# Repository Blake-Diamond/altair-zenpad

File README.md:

# UC Santa Barbara - ECE Department 
## EE Capstone 2018-2019

### Contributors: Evan Blasband, Blake Diamond, Adam Gulliver, Zack Klebanoff

https://capstone.engineering.ucsb.edu/projects/altair-zenpad

This repository contains all of our arduino and android studio code for Altair Zenpad, a smart massage pad that you can control from your fingertips. There are 3 imporant aspect of this respository that contiain all of the necessary reference documents for future development and use of the ZenPad, described below:

## Hardware

PCB/Altair Massage Pad: contains all PCB projects (EAGLE) for Main and Peripheral PCB.

## Firmware

Winter_Demo: This folder contains all of the firmware that is need to flash the Teensy 3.6 using the Arduino IDE. This includes all associated header files that support use of the Bluetooth and PMIC. Some small changes are needed in order to program a Teensy board with the Arduino IDE, which can be found here: https://www.pjrc.com/teensy/tutorial.html

## Software

Zenpad-App/ZenPad: This folder contains the software project for the ZenPad app, which can be accessed by downloading and opening with Android Studio. Someone with Android SW development experience is needed in order to properly open and run the app, which was developed on a Nexus 5 phone.

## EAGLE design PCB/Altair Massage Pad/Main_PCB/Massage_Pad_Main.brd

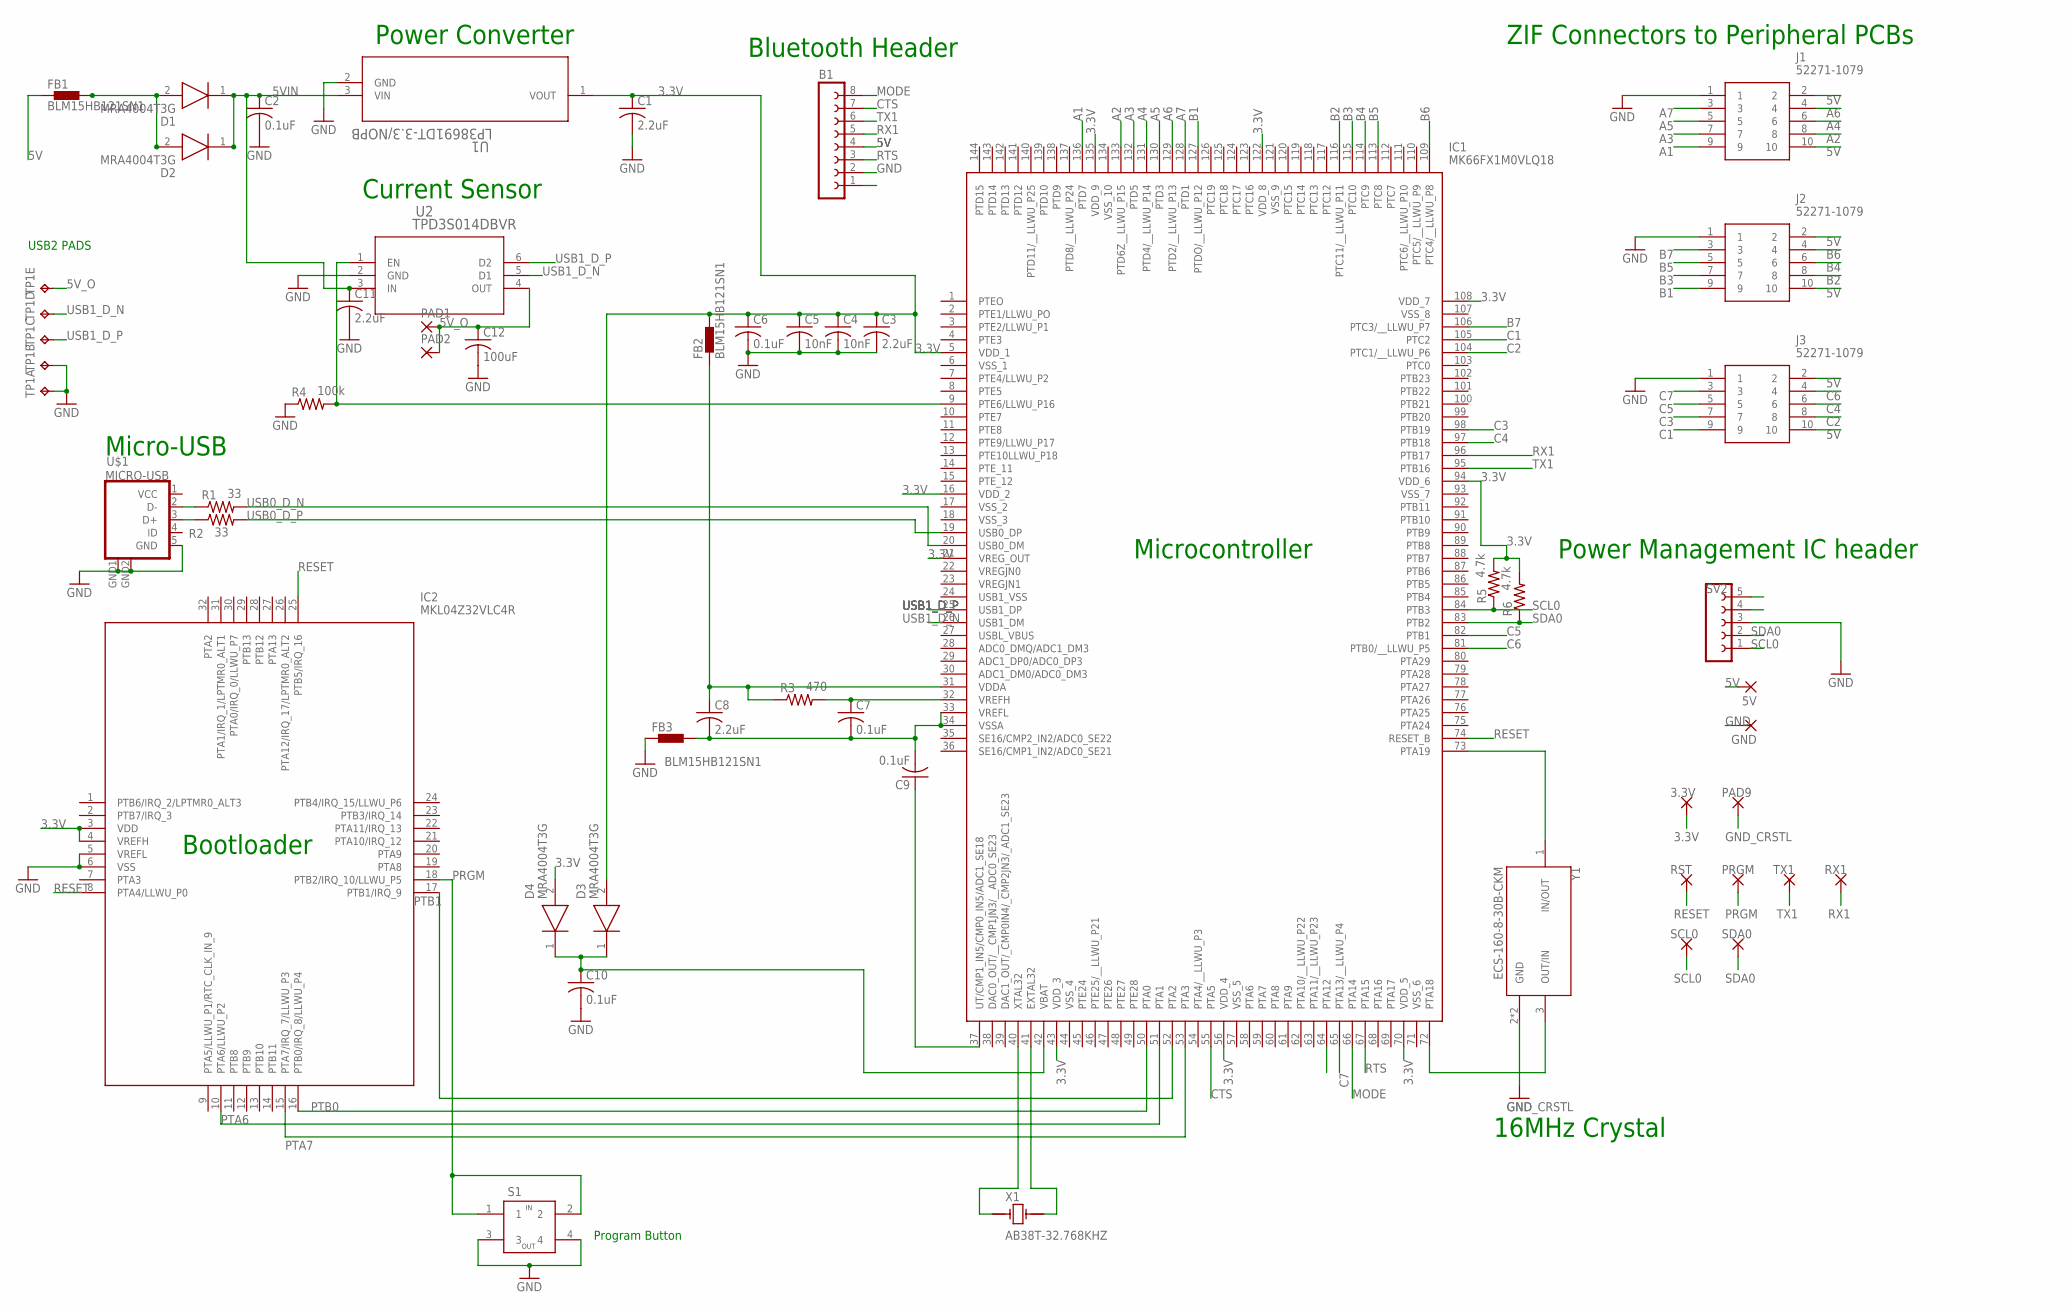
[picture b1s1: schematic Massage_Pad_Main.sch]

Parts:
3.3V: 1,6/0,8
5V: 3,17/1,3
B1: BT-BLE-2479
C1, C3, C8, C11: 2.2uF; C1812K
C2, C6, C7, C9, C10: 0.1uF; C1808
C4, C5: 10nF; C1808
C12: 100uF; C1210K
D1, D2, D3, D4: MRA4004T3G; DIOM5226X220N
FB1, FB2, FB3: BLM15HB121SN1; 0402
GND: 3,17/1,3
IC1: MK66FX1M0VLQ18; QFP50P2200X2200X160-144N
IC2: MKL04Z32VLC4R; QFP80P900X900X160-32N
J1, J2, J3: 52271-1079
PAD1, PAD2: SMD5; SMD2,54-5,08
PAD9: 1,6/0,8
PRGM: 1,6/0,8
R1, R2: 33; R1206
R3: 470; R1206
R4: 100k; R1206
R5, R6: 4.7k; R1206
RST: 1,6/0,8
RX1: 1,6/0,8
S1: RS-187R05A2-DSMTRT
SCL0: 1,6/0,8
SDA0: 1,6/0,8
SV2: FE05-1
TP1: TP5P5-25-13; P5-25-13
TX1: 1,6/0,8
U1: LP38691DT-3.3/NOPB; TD03B
U2: TPD3S014DBVR; DBV6
U$1: MICRO-USB
X1: AB38T-32.768KHZ; XTAL_AB38T-32.768KHZ
Y1: ECS-160-8-30B-CKM; XTAL_ECS-160-8-30B-CKM

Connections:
3.3V: 3.3V.1, C1.1, C3.1, C4.1, C5.1, C6.1, D3.2 (A), D4.2 (A), FB2.2, IC1.5 (VDD_1), IC1.16 (VDD_2), IC1.21 (VREG_OUT), IC1.43 (VDD_3), IC1.56 (VDD_4), IC1.70 (VDD_5), IC1.94 (VDD_6), IC1.108 (VDD_7), IC1.122 (VDD_8), IC1.135 (VDD_9), IC2.3 (VDD), IC2.4 (VREFH), R5.2, R6.2, U1.1 (VOUT)
5V: 5V.1, B1.4, FB1.1, J1.2, J1.10, J2.2, J2.10, J3.2, J3.10
5VIN: C2.1, C11.1, D1.1 (K), D2.1 (K), U1.3 (VIN), U2.3 (IN)
5V_O: C12.1, PAD1.1, PAD2.1, TP1.TP-5, U2.4 (OUT)
A1: IC1.136 (PTD7), J1.9
A2: IC1.133 (PTD6Z__LLWU_P15), J1.8
A3: IC1.132 (PTD5), J1.7
A4: IC1.131 (PTD4/__LLWU_P14), J1.6
A5: IC1.130 (PTD3), J1.5
A6: IC1.129 (PTD2/__LLWU_P13), J1.4
A7: IC1.128 (PTD1), J1.3
B1: IC1.127 (PTDO/__LLWU_P12), J2.9
B2: IC1.116 (PTC11/__LLWU_P11), J2.8
B3: IC1.115 (PTC10), J2.7
B4: IC1.114 (PTC9), J2.6
B5: IC1.113 (PTC8), J2.5
B6: IC1.109 (PTC4/__LLWU_P8), J2.4
B7: IC1.106 (PTC3/__LLWU_P7), J2.3
C1: IC1.105 (PTC2), J3.9
C2: IC1.104 (PTC1/__LLWU_P6), J3.8
C3: IC1.98 (PTB19), J3.7
C4: IC1.97 (PTB18), J3.6
C5: IC1.82 (PTB1), J3.5
C6: IC1.81 (PTB0/__LLWU_P5), J3.4
C7: IC1.65 (PTA13/__LLWU_P4), J3.3
CTS: B1.7, IC1.55 (PTA5)
DFU_5V: B1.1
GND: B1.2, C1.2, C2.2, C3.2, C4.2, C5.2, C6.2, C10.2, C11.2, C12.2, FB3.1, GND.1, IC2.5 (VREFL), IC2.6 (VSS), J1.1, J2.1, J3.1, R4.1, S1.3, S1.4, SV2.3, TP1.TP-1, TP1.TP-2, U1.2 (GND), U2.2 (GND), U$1.5 (GND), U$1.GND1 (GND), U$1.GND2 (GND)
GND_CRSTL: PAD9.1, Y1.2 (GND), Y1.4 (GND)
MODE: B1.8, IC1.66 (PTA14)
unnamed: C10.1, D3.1 (K), D4.1 (K), IC1.42 (VBAT)
unnamed: R1.1, U$1.2 (D-)
unnamed: R2.1, U$1.3 (D+)
unnamed: D1.2 (A), D2.2 (A), FB1.2
unnamed: IC1.73 (PTA19), Y1.1 (IN/OUT)
unnamed: C7.1, IC1.32 (VREFH), R3.2
unnamed: C7.2, C8.2, C9.2, FB3.2, IC1.33 (VREFL), IC1.34 (VSSA)
unnamed: C8.1, FB2.1, IC1.31 (VDDA), R3.1
unnamed: C9.1, IC1.37 (UT/CMP1_IN5/CMP0_IN5/ADC1_SE18)
unnamed: IC1.72 (PTA18), Y1.3 (OUT/IN)
unnamed: IC1.40 (XTAL32), X1.1
unnamed: IC1.41 (EXTAL32), X1.2
unnamed: IC1.9 (PTE6/LLWU_P16), R4.2, U2.1 (EN)
PRGM: IC2.18 (PTB2/IRQ_10/LLWU_P5), PRGM.1, S1.1, S1.2
PTA6: IC1.51 (PTA1), IC2.10 (PTA6/LLWU_P2)
PTA7: IC1.53 (PTA3), IC2.15 (PTA7/IRQ_7/LLWU_P3)
PTB0: IC1.50 (PTA0), IC2.16 (PTB0/IRQ_8/LLWU_P4)
PTB1: IC1.52 (PTA2), IC2.17 (PTB1/IRQ_9)
RESET: IC1.74 (RESET_B), IC2.8 (PTA4/LLWU_P0), IC2.25 (PTB5/IRQ_16), RST.1
RTS: B1.3, IC1.67 (PTA15)
RX1: B1.5, IC1.96 (PTB17), RX1.1
SCL0: IC1.84 (PTB3), R5.1, SCL0.1, SV2.1
SDA0: IC1.83 (PTB2), R6.1, SDA0.1, SV2.2
TX1: B1.6, IC1.95 (PTB16), TX1.1
USB0_D_N: IC1.20 (USB0_DM), R1.2
USB0_D_P: IC1.19 (USB0_DP), R2.2
USB1_D_N: IC1.26 (USB1_DM), TP1.TP-4, U2.5 (D1)
USB1_D_P: IC1.25 (USB1_DP), TP1.TP-3, U2.6 (D2)
VCC: U$1.1 (VCC)

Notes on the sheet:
Bluetooth Header
ZIF Connectors to Peripheral PCBs
Microcontroller
Bootloader
Micro-USB
Power Converter
Current Sensor
Power Management IC header
16MHz Crystal
Program Button
USB2 PADS

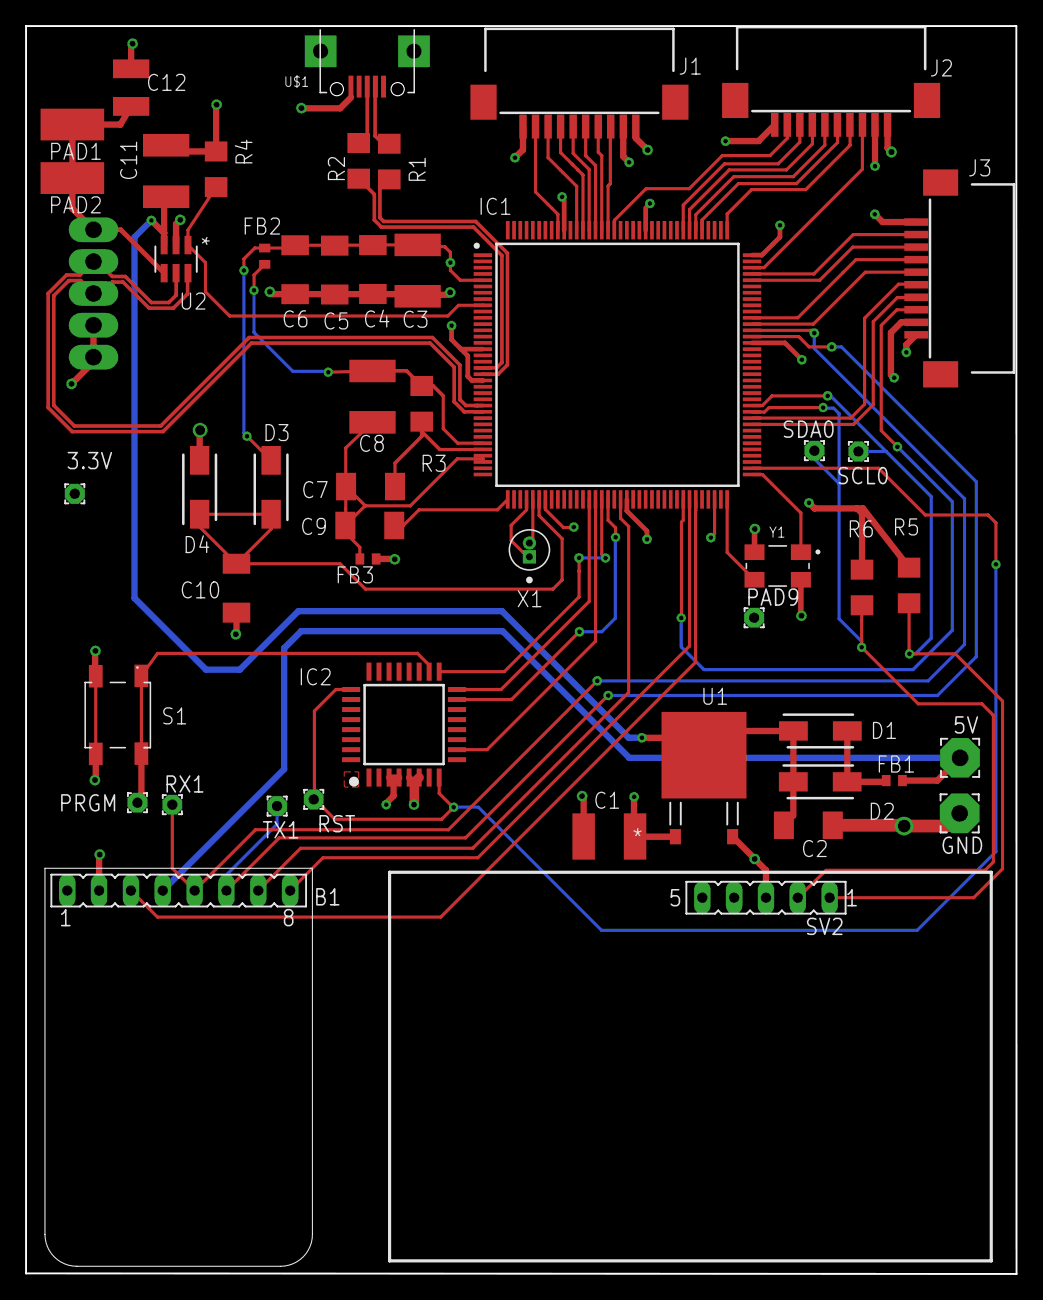
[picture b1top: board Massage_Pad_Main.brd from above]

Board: 4 copper layers, 79.0 x 99.6 mm, 51 parts (0 on the bottom side), 57 nets.

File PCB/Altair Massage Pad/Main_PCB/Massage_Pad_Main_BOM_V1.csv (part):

"Part";"Value";"Device";"Package";"Description";"ALLIED_NUMBER";"ALLIED_PRICE-STOCK";"DESCRIPTION";"DIGI-KEY_PART_NUMBER";"DIGI-KEY_PURCHASE_URL";"HEIGHT";"MANUFACTURER_NAME";"MANUFACTURER_PART_NUMBER";"MF";"MOUSER_PART_NUMBER";"MOUSER_PRICE-STOCK";"MP";"MPN";"OC_FARNELL";"OC_NEWARK";"PACKAGE";"RS_PART_NUMBER";"RS_PRICE-STOCK";"SPICEPREFIX";"TP_SIGNAL_NAME";"VENDOR";
"3.3V";"";"1,6/0,8";"1,6/0,8";"THROUGH-HOLE PAD";"";"";"";"";"";"";"";"";"";"";"";"";"";"";"";"";"";"";"";"";"";
"5V";"";"3,17/1,3";"3,17/1,3";"THROUGH-HOLE PAD";"";"";"";"";"";"";"";"";"";"";"";"";"";"";"";"";"";"";"";"";"";
"B1";"";"BT-BLE-2479";"BT-BLE-2479";"Adafruit bluetooth BLE module for mounting onto PCB.";"";"";"";"";"";"";"";"";"";"";"";"";"";"";"";"";"";"";"";"";"";
"C1";"2.2uF";"C-USC1808";"C1808";"CAPACITOR, American symbol";"";"";"";"";"";"";"";"";"";"";"";"";"";"";"";"";"";"";"C";"";"";
"C2";"0.1uF";"C-USC1808";"C1808";"CAPACITOR, American symbol";"";"";"";"";"";"";"";"";"";"";"";"";"";"";"";"";"";"";"C";"";"";
"C3";"2.2uF";"C-USC1808";"C1808";"CAPACITOR, American symbol";"";"";"";"";"";"";"";"";"";"";"";"";"";"";"";"";"";"";"C";"";"";
"C4";"10nF";"C-USC1808";"C1808";"CAPACITOR, American symbol";"";"";"";"";"";"";"";"";"";"";"";"";"";"";"";"";"";"";"C";"";"";
"C5";"10nF";"C-USC1808";"C1808";"CAPACITOR, American symbol";"";"";"";"";"";"";"";"";"";"";"";"";"";"";"";"";"";"";"C";"";"";
"C6";"0.1uF";"C-USC1808";"C1808";"CAPACITOR, American symbol";"";"";"";"";"";"";"";"";"";"";"";"";"";"";"";"";"";"";"C";"";"";
"C7";"0.1uF";"C-USC1808";"C1808";"CAPACITOR, American symbol";"";"";"";"";"";"";"";"";"";"";"";"";"";"";"";"";"";"";"C";"";"";
"C8";"2.2uF";"C-USC1808";"C1808";"CAPACITOR, American symbol";"";"";"";"";"";"";"";"";"";"";"";"";"";"";"";"";"";"";"C";"";"";
"C9";"0.1uF";"C-USC1808";"C1808";"CAPACITOR, American symbol";"";"";"";"";"";"";"";"";"";"";"";"";"";"";"";"";"";"";"C";"";"";
"C10";"0.1uF";"C-USC1808";"C1808";"CAPACITOR, American symbol";"";"";"";"";"";"";"";"";"";"";"";"";"";"";"";"";"";"";"C";"";"";
"C11";"2.2uF";"C-USC1808";"C1808";"CAPACITOR, American symbol";"";"";"";"";"";"";"";"";"";"";"";"";"";"";"";"";"";"";"C";"";"";
"C12";"100uF";"C-USC1808";"C1808";"CAPACITOR, American symbol";"";"";"";"";"";"";"";"";"";"";"";"";"";"";"";"";"";"";"C";"";"";
"D1";"MRA4004T3G";"MRA4004T3G";"DIOM5226X220N";"Rectifier diode,MRA4004 1A 400V ON Semi MRA4004T3G, SMT Switching Diode, 400V 1A, 2-Pin DO-214AC";"70340468";"http://www.alliedelec.com/on-semiconductor-mra4004t3g/70340468/";"Rectifier diode,MRA4004 1A 400V ON Semi MRA4004T3G, SMT Switching Diode, 400V 1A, 2-Pin DO-214AC";"";"";"2.2mm";"ON Semiconductor";"MRA4004T3G";"";"863-MRA4004T3G";"https://www.mouser.com/Search/Refine.aspx?Keyword=863-MRA4004T3G";"";"";"";"";"";"6490904";"http://uk.rs-online.com/web/p/products/6490904";"";"";"";
"D2";"MRA4004T3G";"MRA4004T3G";"DIOM5226X220N";"Rectifier diode,MRA4004 1A 400V ON Semi MRA4004T3G, SMT Switching Diode, 400V 1A, 2-Pin DO-214AC";"70340468";"http://www.alliedelec.com/on-semiconductor-mra4004t3g/70340468/";"Rectifier diode,MRA4004 1A 400V ON Semi MRA4004T3G, SMT Switching Diode, 400V 1A, 2-Pin DO-214AC";"";"";"2.2mm";"ON Semiconductor";"MRA4004T3G";"";"863-MRA4004T3G";"https://www.mouser.com/Search/Refine.aspx?Keyword=863-MRA4004T3G";"";"";"";"";"";"6490904";"http://uk.rs-online.com/web/p/products/6490904";"";"";"";
"D3";"MRA4004T3G";"MRA4004T3G";"DIOM5226X220N";"Rectifier diode,MRA4004 1A 400V ON Semi MRA4004T3G, SMT Switching Diode, 400V 1A, 2-Pin DO-214AC";"70340468";"http://www.alliedelec.com/on-semiconductor-mra4004t3g/70340468/";"Rectifier diode,MRA4004 1A 400V ON Semi MRA4004T3G, SMT Switching Diode, 400V 1A, 2-Pin DO-214AC";"";"";"2.2mm";"ON Semiconductor";"MRA4004T3G";"";"863-MRA4004T3G";"https://www.mouser.com/Search/Refine.aspx?Keyword=863-MRA4004T3G";"";"";"";"";"";"6490904";"http://uk.rs-online.com/web/p/products/6490904";"";"";"";
"D4";"MRA4004T3G";"MRA4004T3G";"DIOM5226X220N";"Rectifier diode,MRA4004 1A 400V ON Semi MRA4004T3G, SMT Switching Diode, 400V 1A, 2-Pin DO-214AC";"70340468";"http://www.alliedelec.com/on-semiconductor-mra4004t3g/70340468/";"Rectifier diode,MRA4004 1A 400V ON Semi MRA4004T3G, SMT Switching Diode, 400V 1A, 2-Pin DO-214AC";"";"";"2.2mm";"ON Semiconductor";"MRA4004T3G";"";"863-MRA4004T3G";"https://www.mouser.com/Search/Refine.aspx?Keyword=863-MRA4004T3G";"";"";"";"";"";"6490904";"http://uk.rs-online.com/web/p/products/6490904";"";"";"";
"FB1";"BLM15HB121SN1";"BLM15HB121SN1";"0402";"EMIFIL (R) Chip Ferrite Bead for GHz Noise";"";"";"";"";"";"";"";"";"";"";"";"";"";"";"";"";"";"";"";"";"";
"FB2";"BLM15HB121SN1";"BLM15HB121SN1";"0402";"EMIFIL (R) Chip Ferrite Bead for GHz Noise";"";"";"";"";"";"";"";"";"";"";"";"";"";"";"";"";"";"";"";"";"";
"FB3";"BLM15HB121SN1";"BLM15HB121SN1";"0402";"EMIFIL (R) Chip Ferrite Bead for GHz Noise";"";"";"";"";"";"";"";"";"";"";"";"";"";"";"";"";"";"";"";"";"";
"GND";"";"3,17/1,3";"3,17/1,3";"THROUGH-HOLE PAD";"";"";"";"";"";"";"";"";"";"";"";"";"";"";"";"";"";"";"";"";"";
"IC1";"MK66FX1M0VLQ18";"MK66FX1M0VLQ18";"QFP50P2200X2200X160-144N";"NXP - MK66FX1M0VLQ18 - MPU, ARM CORTEX-M4F, 180MHZ, LQFP-144";"";"";"NXP - MK66FX1M0VLQ18 - MPU, ARM CORTEX-M4F, 180MHZ, LQFP-144";"";"";"1.6mm";"Nexperia";"MK66FX1M0VLQ18";"";"841-MK66FX1M0VLQ18";"https://www.mouser.com/Search/Refine.aspx?Keyword=841-MK66FX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";"";"";"";"";"";"";"";"";"";"";
"IC2";"MKL04Z32VLC4R";"MKL04Z32VLC4R";"QFP80P900X900X160-32N";"IC MCU 32BIT 32KB FLASH 32LQFP";"";"";"IC MCU 32BIT 32KB FLASH 32LQFP";"";"";"1.6mm";"Nexperia";"MKL04Z32VLC4R";"";"N/A";"https://www.mouser.com/Search/Refine.aspx?Keyword=N%2FA";"";"";"";"";"";"";"";"";"";"";
"J1";"52271-1079";"52271-1079";"52271-1079";"1.0MM FPC  R/A CONN 10 W Molex FFC/FPC SMT Series 1mm Pitch 10 Way Right Angle SMT Female FPC Connector, ZIF Bottom Contact";"70373119";"https://www.alliedelec.com/molex-incorporated-52271-1079/70373119/";"1.0MM FPC  R/A CONN 10 W Molex FFC/FPC SMT Series 1mm Pitch 10 Way Right Angle SMT Female FPC Connector, ZIF Bottom Contact";"";"";"mm";"Molex";"52271-1079";"";"538-52271-1079";"https://www.mouser.com/Search/Refine.aspx?Keyword=538-52271-1079";"";"";"";"";"";"5144329P";"http://uk.rs-online.com/web/p/products/5144329P";"";"";"";
"J2";"52271-1079";"52271-1079";"52271-1079";"1.0MM FPC  R/A CONN 10 W Molex FFC/FPC SMT Series 1mm Pitch 10 Way Right Angle SMT Female FPC Connector, ZIF Bottom Contact";"70373119";"https://www.alliedelec.com/molex-incorporated-52271-1079/70373119/";"1.0MM FPC  R/A CONN 10 W Molex FFC/FPC SMT Series 1mm Pitch 10 Way Right Angle SMT Female FPC Connector, ZIF Bottom Contact";"";"";"mm";"Molex";"52271-1079";"";"538-52271-1079";"https://www.mouser.com/Search/Refine.aspx?Keyword=538-52271-1079";"";"";"";"";"";"5144329P";"http://uk.rs-online.com/web/p/products/5144329P";"";"";"";
"J3";"52271-1079";"52271-1079";"52271-1079";"1.0MM FPC  R/A CONN 10 W Molex FFC/FPC SMT Series 1mm Pitch 10 Way Right Angle SMT Female FPC Connector, ZIF Bottom Contact";"70373119";"https://www.alliedelec.com/molex-incorporated-52271-1079/70373119/";"1.0MM FPC  R/A CONN 10 W Molex FFC/FPC SMT Series 1mm Pitch 10 Way Right Angle SMT Female FPC Connector, ZIF Bottom Contact";"";"";"mm";"Molex";"52271-1079";"";"538-52271-1079";"https://www.mouser.com/Search/Refine.aspx?Keyword=538-52271-1079";"";"";"";"";"";"5144329P";"http://uk.rs-online.com/web/p/products/5144329P";"";"";"";
"PAD1";"";"SMD5";"SMD2,54-5,08";"SMD PAD";"";"";"";"";"";"";"";"";"";"";"";"";"";"";"";"";"";"";"";"";"";
"PAD2";"";"SMD5";"SMD2,54-5,08";"SMD PAD";"";"";"";"";"";"";"";"";"";"";"";"";"";"";"";"";"";"";"";"";"";
"PAD9";"";"1,6/0,8";"1,6/0,8";"THROUGH-HOLE PAD";"";"";"";"";"";"";"";"";"";"";"";"";"";"";"";"";"";"";"";"";"";
"PRGM";"";"1,6/0,8";"1,6/0,8";"THROUGH-HOLE PAD";"";"";"";"";"";"";"";"";"";"";"";"";"";"";"";"";"";"";"";"";"";
"R1";"33";"R-EU_MELF0207W";"MINI_MELF-0207W";"RESISTOR, European symbol";"";"";"";"";"";"";"";"";"";"";"";"";"";"";"";"";"";"";"";"";"";
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
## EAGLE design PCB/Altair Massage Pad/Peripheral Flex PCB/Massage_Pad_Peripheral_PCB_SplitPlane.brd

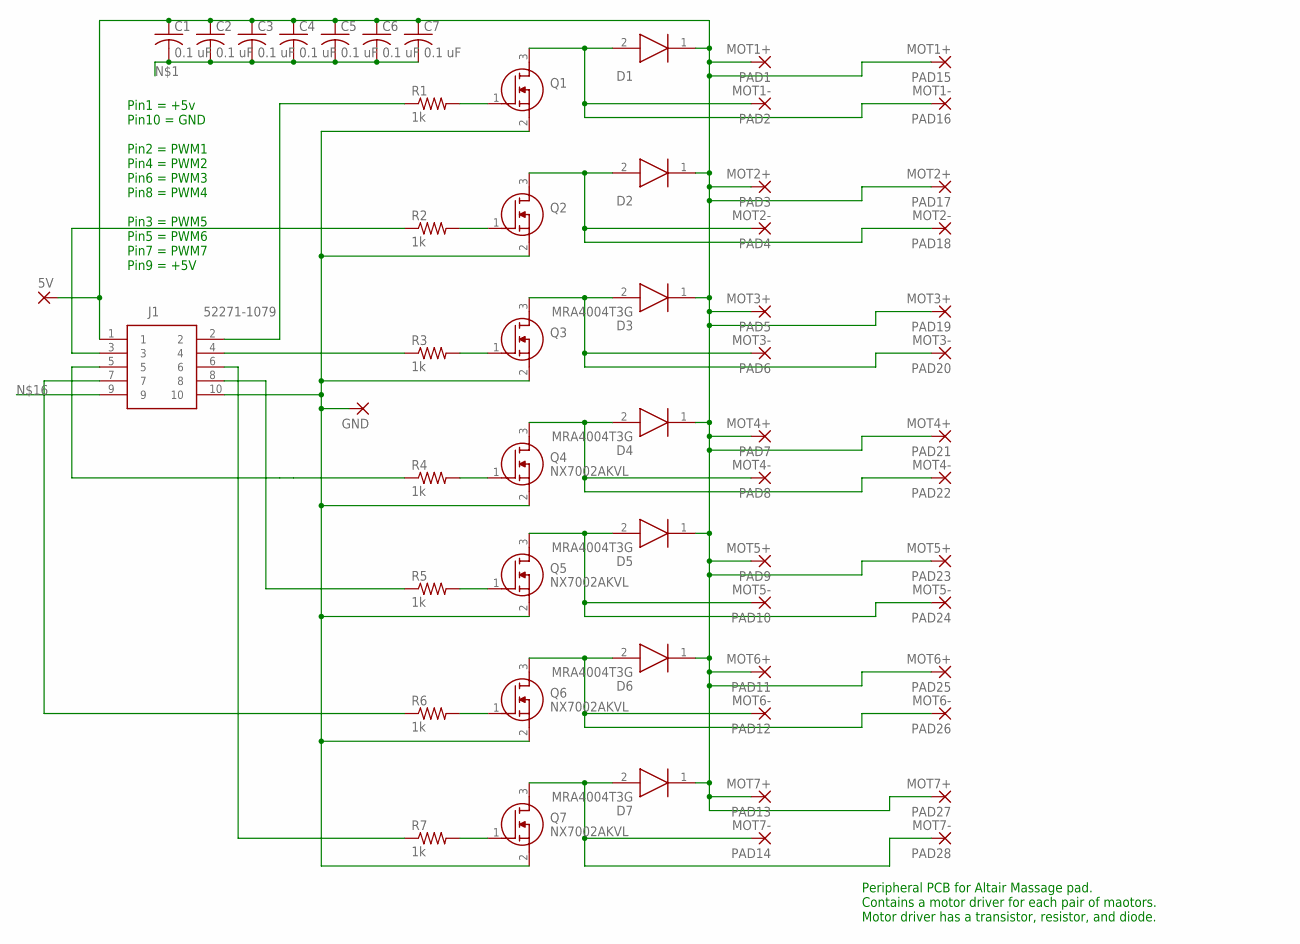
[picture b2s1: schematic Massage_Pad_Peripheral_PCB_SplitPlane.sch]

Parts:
5V: 3,17/1,3
C1, C2, C3, C4, C5, C6, C7: 0.1 uF; C1808; MANUFACTURER_PART_NUMBER C1808C104K5RACTU; MOUSER_PART_NUMBER 80-C1808C104K5R
D1, D2, D3, D4, D5, D6, D7: MRA4004T3G; DIOM5226X220N
GND: 3,17/1,3
J1: 52271-1079
PAD1, PAD15: MOT1+; 5-2,5
PAD2, PAD16: MOT1-; 5-2,5
PAD3, PAD17: MOT2+; 5-2,5
PAD4, PAD18: MOT2-; 5-2,5
PAD5, PAD19: MOT3+; 5-2,5
PAD6, PAD20: MOT3-; 5-2,5
PAD7, PAD21: MOT4+; 5-2,5
PAD8, PAD22: MOT4-; 5-2,5
PAD9, PAD23: MOT5+; 5-2,5
PAD10, PAD24: MOT5-; 5-2,5
PAD11, PAD25: MOT6+; 5-2,5
PAD12, PAD26: MOT6-; 5-2,5
PAD13, PAD27: MOT7+; 5-2,5
PAD14, PAD28: MOT7-; 5-2,5
Q1, Q2, Q3, Q4, Q5, Q6, Q7: NX7002AKVL; SOT95P230X110-3N
R1: 1k; R1206; MANUFACTURER_PART_NUMBER CR1206-FX-1001ELF; MOUSER_PART_NUMBER 652-CR1206FX-1001ELF
R2, R3, R4, R5, R6, R7: 1k; R1206

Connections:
unnamed: C1.2, C2.2, C3.2, C4.2, C5.2, C6.2, C7.2, GND.1, J1.10, Q1.2 (S), Q2.2 (S), Q3.2 (S), Q4.2 (S), Q5.2 (S), Q6.2 (S), Q7.2 (S)
unnamed: Q1.1 (G), R1.2
unnamed: Q2.1 (G), R2.2
unnamed: Q3.1 (G), R3.2
unnamed: Q4.1 (G), R4.2
unnamed: Q5.1 (G), R5.2
unnamed: Q6.1 (G), R6.2
unnamed: Q7.1 (G), R7.2
unnamed: D7.2 (A), PAD14.1, PAD28.1, Q7.3 (D)
unnamed: D6.2 (A), PAD12.1, PAD26.1, Q6.3 (D)
unnamed: D5.2 (A), PAD10.1, PAD24.1, Q5.3 (D)
unnamed: D3.2 (A), PAD6.1, PAD20.1, Q3.3 (D)
unnamed: D4.2 (A), PAD8.1, PAD22.1, Q4.3 (D)
unnamed: D2.2 (A), PAD4.1, PAD18.1, Q2.3 (D)
unnamed: D1.2 (A), PAD2.1, PAD16.1, Q1.3 (D)
unnamed: 5V.1, C1.1, C2.1, C3.1, C4.1, C5.1, C6.1, C7.1, D1.1 (K), D2.1 (K), D3.1 (K), D4.1 (K), D5.1 (K), D6.1 (K), D7.1 (K), J1.1, J1.9, PAD1.1, PAD3.1, PAD5.1, PAD7.1, PAD9.1, PAD11.1, PAD13.1, PAD15.1, PAD17.1, PAD19.1, PAD21.1, PAD23.1, PAD25.1, PAD27.1
unnamed: J1.2, R1.1
unnamed: J1.3, R2.1
unnamed: J1.4, R3.1
unnamed: J1.5, R4.1
unnamed: J1.8, R5.1
unnamed: J1.7, R6.1
unnamed: J1.6, R7.1

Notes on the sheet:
Peripheral PCB for Altair Massage pad. Contains a motor driver for each pair of maotors. Motor driver has a transistor, resistor, and diode.
Pin1 = +5v Pin10 = GND Pin2 = PWM1 Pin4 = PWM2 Pin6 = PWM3 Pin8 = PWM4 Pin3 = PWM5 Pin5 = PWM6 Pin7 = PWM7 Pin9 = +5V

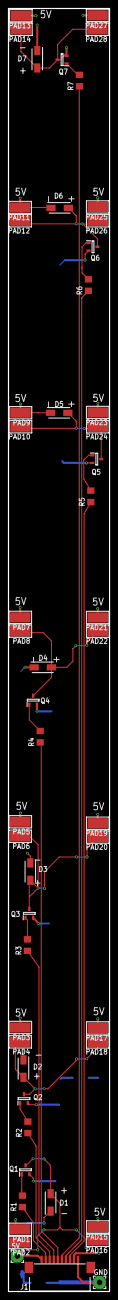
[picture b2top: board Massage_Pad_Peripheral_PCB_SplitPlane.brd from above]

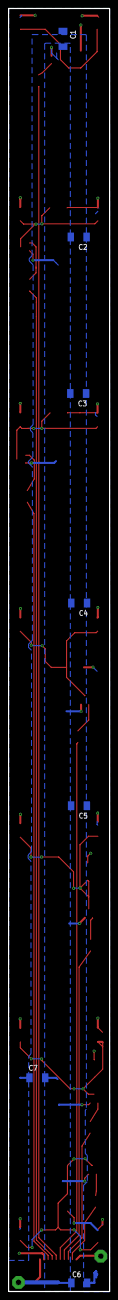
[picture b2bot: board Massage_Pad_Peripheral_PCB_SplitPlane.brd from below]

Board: 2 copper layers, 25.0 x 317.5 mm, 59 parts (7 on the bottom side), 23 nets.

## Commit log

2019-03-17 bluefruit example
2019-03-17 Rename BluefruitConfig.h to Bluetooth/BluefruitConfig.h
2019-03-17 reorganize
2019-03-17 Rename PMIC.h to PMIC/PMIC.h
2019-03-19 moved file into folder
2019-03-21 explanation
2019-03-21 3/20/19
2019-05-13 Create Zenpad-Android-App
2019-05-13 Create ZenPad-Bluetooth-Demo
2019-05-13 Create test
2019-05-14 Add files via upload
    Updates to Teensy firmware to read and print multiple bytes sent from BLE. Added needed adafruit library for arduino compatibility
2019-05-14 slight android updates to send multiple bytes via BLE
2019-05-14 Files for main PCB and Peripheral PCB sent for fab
2019-05-15 Template App for ZenPad
2019-05-17 integrated layout with BLE capability, still incomplete
2019-05-19 prints basic characters from app
2019-05-20 seekbar scaling and firmware cases handled
2019-05-21 custom activity ready for test, FW has all branches
2019-05-21 functionally complete, not tested
2019-05-22 functionally complete & tested, UI needs improvement
2019-05-22 firmware complete with patterns, needs testing
2019-05-22 removed while loop bug
2019-05-23 added onClick for all buttons, fixed FAB color
2019-05-29 code from altair demo
2019-05-30 check Vertical Wave, could try interrupt on RTS
2019-06-05 Improved Vertical Wave
2019-06-06 Small update to the pattern calls to chek for continuation
2019-09-17 creating file with media like pictures, poster etc. video too large to push so it is not included
